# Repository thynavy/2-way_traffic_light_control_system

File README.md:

# 2-Way Traffic Light System Using IC 4017, 555 Timer, and Diodes

## Project Overview

This project demonstrates a **2-way traffic light control system** using a 4017 Decade Counter, 555 Timer IC, and diodes. The circuit simulates a traffic light sequence for a 2-way intersection with two sets of red, yellow, and green LEDs. Each set changes automatically based on a timed sequence, making this an effective model for traffic light operation.
<p align="center">
    
    <br />
    <strong>Figure 1: The 2-way traffic light control system</strong>
</p>
<p align="center">
    
    <br />
    <strong>Figure 2: Traffic Light LED</strong>
</p>

## Features

- **Automated Traffic Light Sequence:** Operates two sets of traffic lights (each with red, yellow, and green LEDs) in a timed sequence, simulating real-world traffic control.
- **Diode Isolation:** Diodes are used to control the LED flow and prevent reverse currents, ensuring stable operation and extending the lifespan of the LEDs.
- **Adjustable Timing:** A potentiometer allows for fine-tuning of the 555 timer's clock speed, which controls the timing of each LED, enabling customizable light intervals.
- **Efficient Design:** Built with minimal components around two popular ICs—the 4017 and the 555 timer—plus diodes, making it a beginner-friendly yet reliable project.

## Components Used

- **IC 4017 Decade Counter:** Cycles through 10 output pins (Q0 to Q9) with each clock pulse, enabling controlled LED sequencing for the traffic lights.
- **IC 555 Timer:** Configured in astable mode to generate a continuous clock pulse that drives the 4017 counter. The clock pulse timing determines the LED switching rate.
- **Diodes:** Diodes are included to manage the current flow between LEDs and outputs of the 4017, isolating each LED to avoid interference or backfeeding between the outputs.
- **LEDs:** Two sets of red, yellow, and green LEDs represent the two traffic lights, each controlled by specific 4017 output pins.
- **Resistors and Capacitors:** Used for LED current limiting and for setting the timing interval on the 555 timer.

## How It Works

1. Clock Generation with the 555 Timer: The 555 timer provides a steady clock pulse to the 4017. The pulse frequency can be adjusted with a potentiometer, allowing for customized traffic light intervals.
2. LED Sequence Control with the 4017 Decade Counter: Clock pulses advance the 4017 through its output pins (Q0 to Q9), each of which lights up a specific LED in sequence.
3. Diode Isolation:
   - Diodes are placed on certain output pins of the 4017 to prevent backfeeding, ensuring each LED only receives current from its intended output pin.
   - This prevents one traffic light’s signal from affecting the other, ensuring that each set of LEDs operates independently without cross-interference.
4. Traffic Light Logic:
   - The first traffic light is controlled by outputs Q0, Q1, and Q2, which turn on the red, yellow, and green LEDs in sequence.
   - The second traffic light is managed by outputs Q3, Q4, and Q5, with its own red, yellow, and green LEDs.
   - After Q5, the 4017 resets to Q0, creating a continuous cycle.

This circuit serves as an excellent demonstration of timing control, current management using diodes, and sequencing for traffic applications. It’s a practical project for anyone learning about digital logic, timing circuits, and diode use for current isolation.

## Documentations

[Schematic (PDF)](https://github.com/thynavy/2-way_traffic_light_control_system/blob/main/4017.pdf)

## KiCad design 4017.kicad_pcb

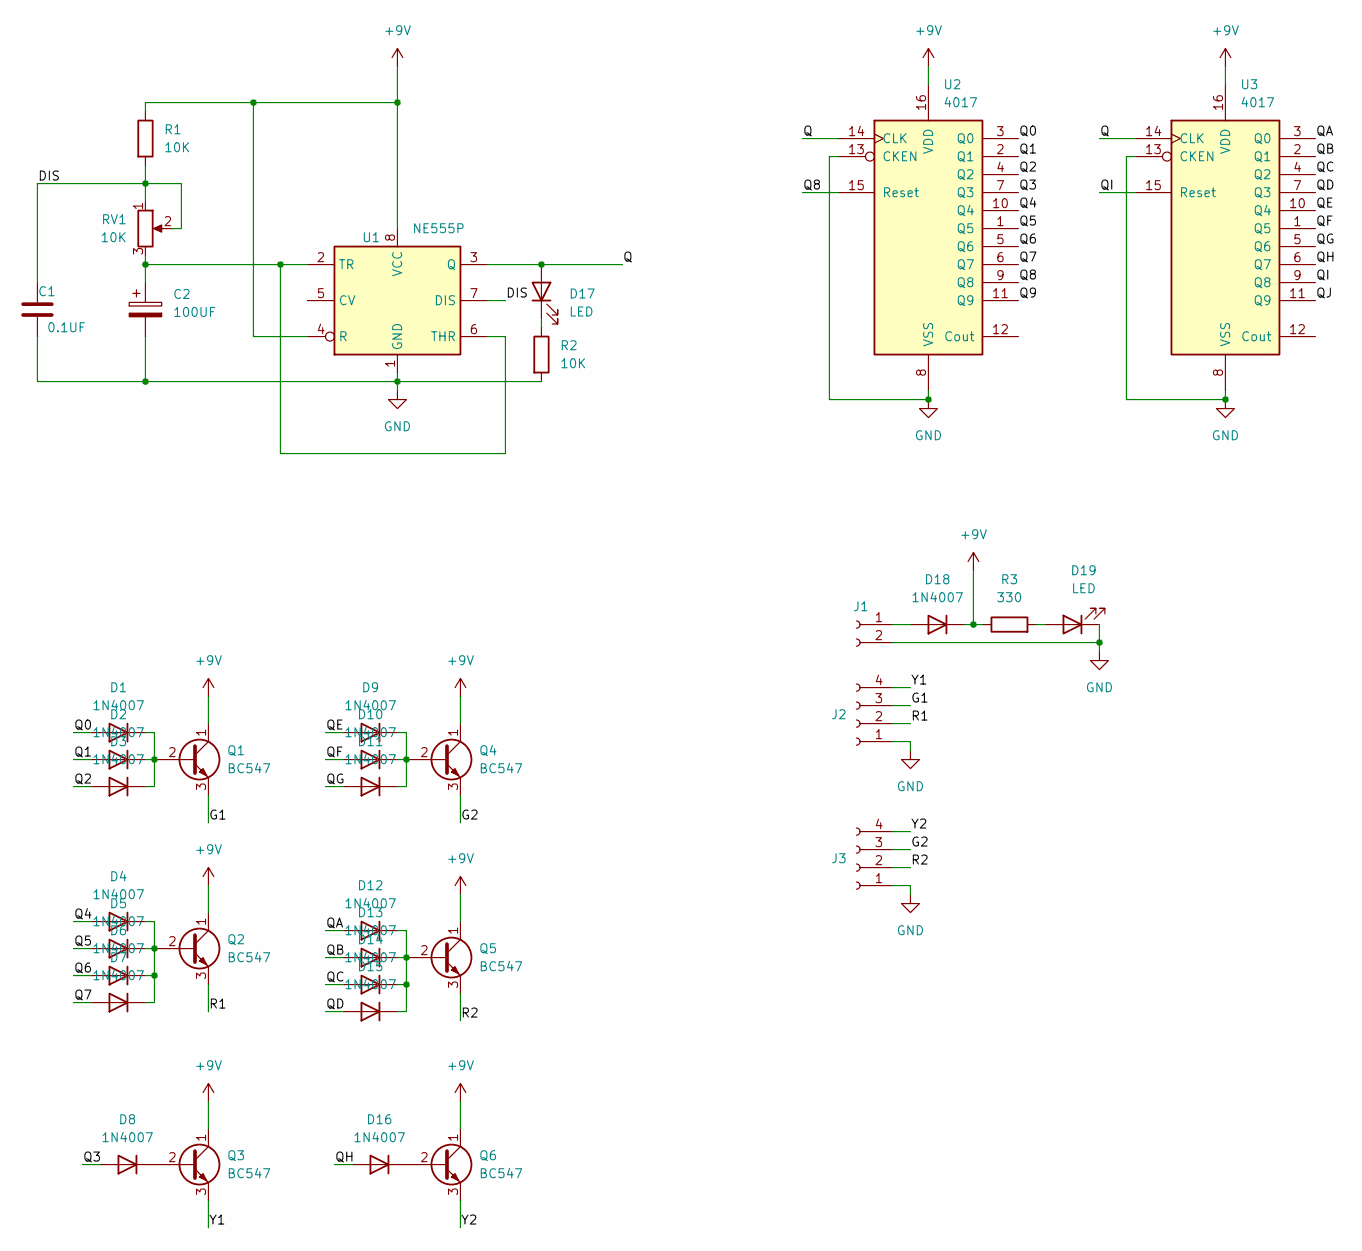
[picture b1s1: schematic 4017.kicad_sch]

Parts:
C1: 0.1UF; C_Disc_D5.0mm_W2.5mm_P5.00mm
C2: 100UF; CP_Radial_D7.5mm_P2.50mm
D1, D2, D3, D4, D5, D6, D7, D8, D9, D10, D11, D12, D13, D14, D15, D16, D18: 1N4007; D_DO-41_SOD81_P10.16mm_Horizontal
D17, D19: LED; LED_D3.0mm
J1: Conn_01x02_Female; JST_XH_B2B-XH-A_1x02_P2.50mm_Vertical
J2, J3: Conn_01x04_Female; JST_XH_B4B-XH-A_1x04_P2.50mm_Vertical
Q1, Q2, Q3, Q4, Q5, Q6: BC547; TO-92_Inline
R1, R2: 10K; R_Axial_DIN0207_L6.3mm_D2.5mm_P7.62mm_Horizontal
R3: 330; R_Axial_DIN0207_L6.3mm_D2.5mm_P7.62mm_Horizontal
RV1: 10K; Potentiometer_Bourns_3296W_Vertical
U1: NE555P; DIP-8_W7.62mm
U2, U3: 4017; DIP-16_W7.62mm_LongPads

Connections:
+9V: D18.1 (K), Q1.1 (C), Q2.1 (C), Q3.1 (C), Q4.1 (C), Q5.1 (C), Q6.1 (C), R1.1, R3.1, U1.4 (R), U1.8 (VCC), U2.16 (VDD), U3.16 (VDD)
/DIS: C1.1, R1.2, RV1.1, RV1.2, U1.7 (DIS)
/G1: J2.3, Q1.3 (E)
/G2: J3.3, Q4.3 (E)
/Q0: D1.2 (A), U2.3 (Q0)
/Q1: D2.2 (A), U2.2 (Q1)
/Q2: D3.2 (A), U2.4 (Q2)
/Q3: D8.2 (A), U2.7 (Q3)
/Q4: D4.2 (A), U2.10 (Q4)
/Q5: D5.2 (A), U2.1 (Q5)
/Q6: D6.2 (A), U2.5 (Q6)
/Q7: D7.2 (A), U2.6 (Q7)
/Q8: U2.9 (Q8), U2.15 (Reset)
/Q9: U2.11 (Q9)
/QA: D12.2 (A), U3.3 (Q0)
/QB: D13.2 (A), U3.2 (Q1)
/QC: D14.2 (A), U3.4 (Q2)
/QD: D15.2 (A), U3.7 (Q3)
/QE: D9.2 (A), U3.10 (Q4)
/QF: D10.2 (A), U3.1 (Q5)
/QG: D11.2 (A), U3.5 (Q6)
/QH: D16.2 (A), U3.6 (Q7)
/QI: U3.9 (Q8), U3.15 (Reset)
/QJ: U3.11 (Q9)
/R1: J2.2, Q2.3 (E)
/R2: J3.2, Q5.3 (E)
/Y1: J2.4, Q3.3 (E)
/Y2: J3.4, Q6.3 (E)
GND: C1.2, C2.2, D19.1 (K), J1.2, J2.1, J3.1, R2.2, U1.1 (GND), U2.8 (VSS), U2.13 (CKEN), U3.8 (VSS), U3.13 (CKEN)
unnamed: C2.1, RV1.3, U1.2 (TR), U1.6 (THR)
unnamed: D1.1 (K), D2.1 (K), D3.1 (K), Q1.2 (B)
unnamed: D4.1 (K), D5.1 (K), D6.1 (K), D7.1 (K), Q2.2 (B)
unnamed: D8.1 (K), Q3.2 (B)
unnamed: D9.1 (K), D10.1 (K), D11.1 (K), Q4.2 (B)
unnamed: D12.1 (K), D13.1 (K), D14.1 (K), D15.1 (K), Q5.2 (B)
unnamed: D16.1 (K), Q6.2 (B)
unnamed: D18.2 (A), J1.1
unnamed: D19.2 (A), R3.2

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
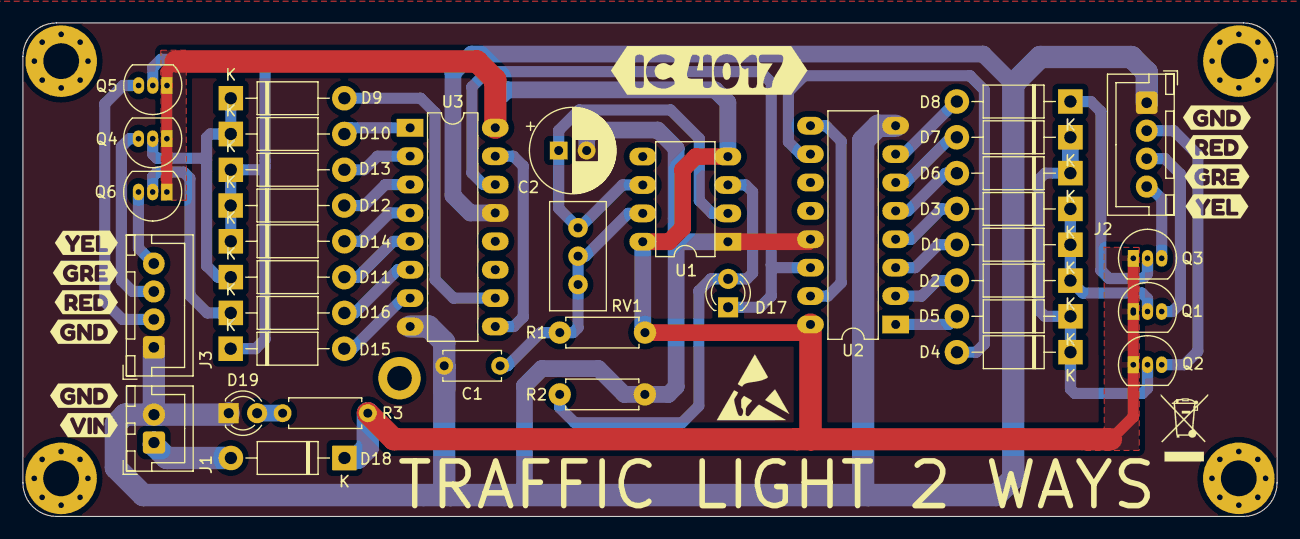
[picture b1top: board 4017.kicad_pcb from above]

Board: 2 copper layers, 112.2 x 44.2 mm, 48 parts (0 on the bottom side), 38 nets.

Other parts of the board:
kibuzzard-6729E5F1: G***; kibuzzard-6729E5F1
kibuzzard-6729E51F, kibuzzard-6729E51F#2: G***; kibuzzard-6729E51F
kibuzzard-6729E504, kibuzzard-6729E504#2, kibuzzard-6729E504#3: G***; kibuzzard-6729E504
kibuzzard-6729E532, kibuzzard-6729E532#2: G***; kibuzzard-6729E532
kibuzzard-6729E545, kibuzzard-6729E545#2: G***; kibuzzard-6729E545
kibuzzard-6729E654: G***; kibuzzard-6729E654
